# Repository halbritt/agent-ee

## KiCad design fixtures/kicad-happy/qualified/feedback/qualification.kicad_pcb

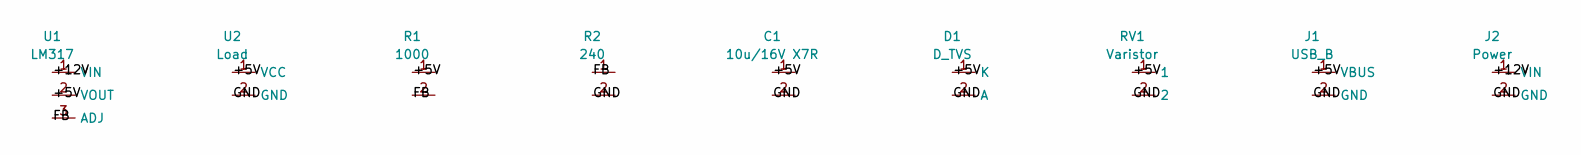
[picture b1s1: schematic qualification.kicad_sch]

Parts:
C1: 10u/16V X7R; C_0805
D1: D_TVS; D
J1: USB_B; USB
J2: Power; Conn
R1: 1000; R_0805
R2: 240; R_0805
RV1: Varistor; RV
U1: LM317; SOT-223
U2: Load

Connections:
+5V: C1.1, D1.1 (K), J1.1 (VBUS), R1.1, RV1.1, U1.2 (VOUT), U2.1 (VCC)
+12V: J2.1 (VIN), U1.1 (VIN)
FB: R1.2, R2.1, U1.3 (ADJ)
GND: C1.2, D1.2 (A), J1.2 (GND), J2.2 (GND), R2.2, RV1.2, U2.2 (GND)

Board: 2 copper layers, 9 parts (0 on the bottom side), 4 nets, no tracks yet.

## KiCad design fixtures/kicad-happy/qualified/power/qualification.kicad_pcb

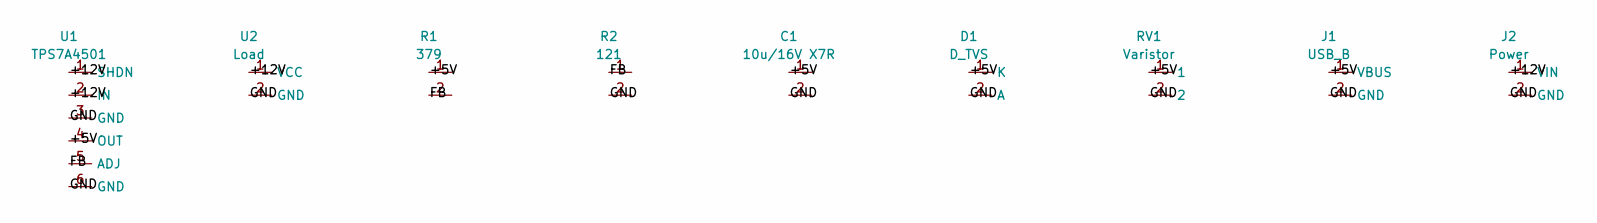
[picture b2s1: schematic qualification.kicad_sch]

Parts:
C1: 10u/16V X7R; C_0805
D1: D_TVS; D
J1: USB_B; USB
J2: Power; Conn
R1: 379; R_0805
R2: 121; R_0805
RV1: Varistor; RV
U1: TPS7A4501; SOT-223
U2: Load

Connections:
+5V: C1.1, D1.1 (K), J1.1 (VBUS), R1.1, RV1.1, U1.4 (OUT)
+12V: J2.1 (VIN), U1.1 (SHDN), U1.2 (IN), U2.1 (VCC)
FB: R1.2, R2.1, U1.5 (ADJ)
GND: C1.2, D1.2 (A), J1.2 (GND), J2.2 (GND), R2.2, RV1.2, U1.3 (GND), U1.6 (GND), U2.2 (GND)

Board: 2 copper layers, 9 parts (0 on the bottom side), 4 nets, no tracks yet.

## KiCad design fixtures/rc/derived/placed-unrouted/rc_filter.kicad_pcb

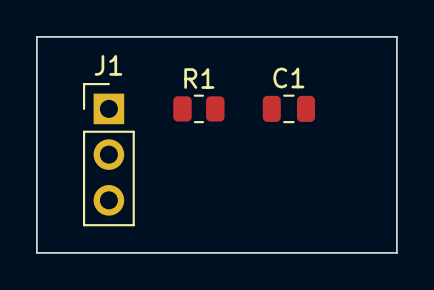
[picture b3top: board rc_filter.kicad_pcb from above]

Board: 2 copper layers, 20.0 x 12.0 mm, 3 parts (0 on the bottom side), 3 nets, no tracks yet.

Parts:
C1: 100n; C_0805_2012Metric
J1: Conn_01x03; PinHeader_1x03_P2.54mm_Vertical
R1: 10k; R_0805_2012Metric

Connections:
/IN: J1.1, R1.1
/OUT: C1.1, J1.2, R1.2
GND: C1.2, J1.3
